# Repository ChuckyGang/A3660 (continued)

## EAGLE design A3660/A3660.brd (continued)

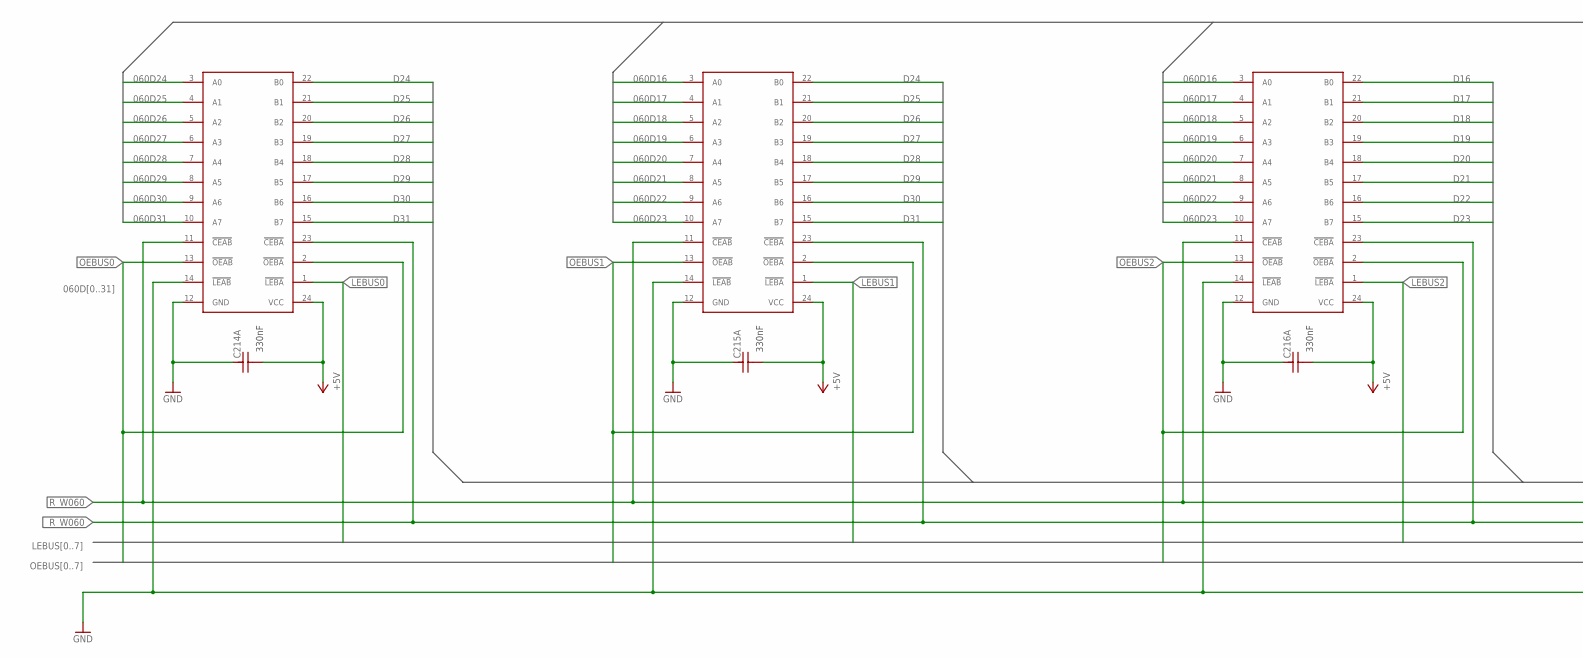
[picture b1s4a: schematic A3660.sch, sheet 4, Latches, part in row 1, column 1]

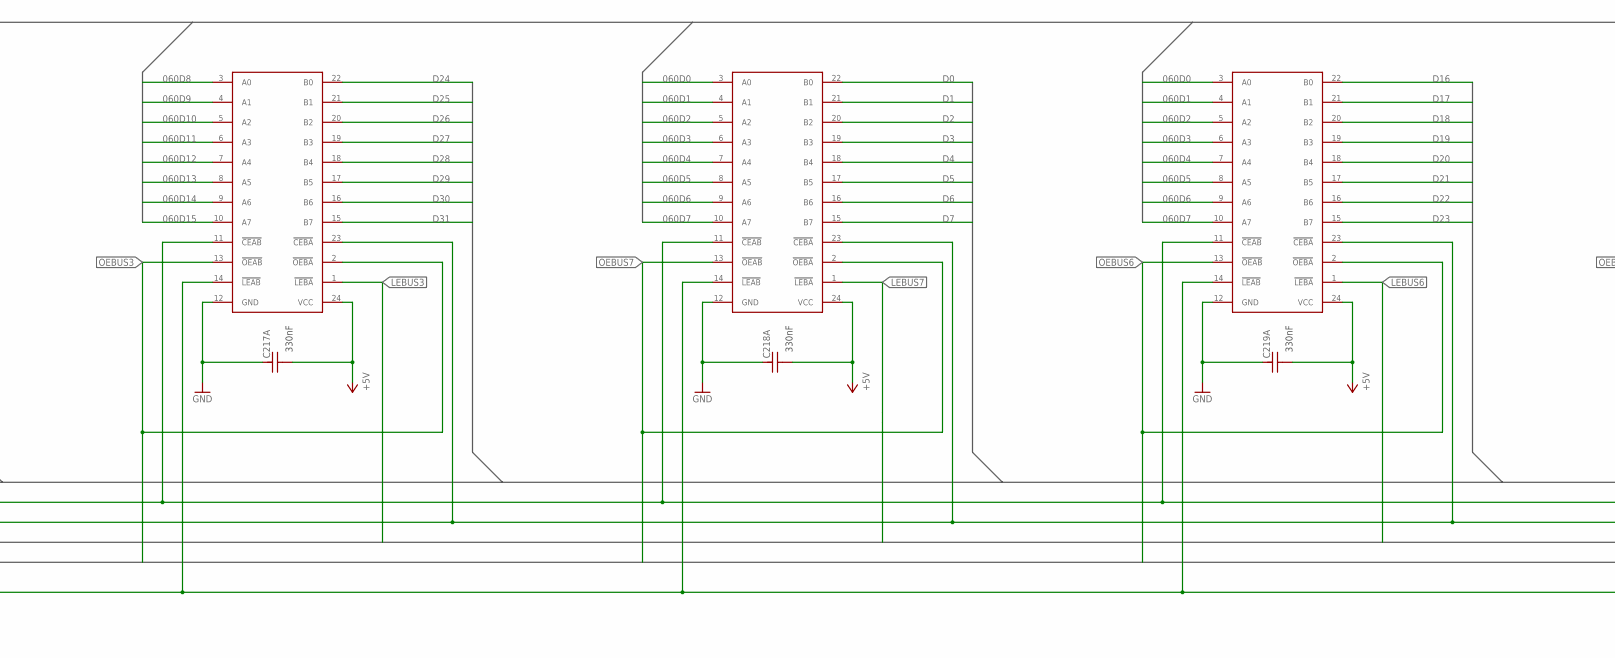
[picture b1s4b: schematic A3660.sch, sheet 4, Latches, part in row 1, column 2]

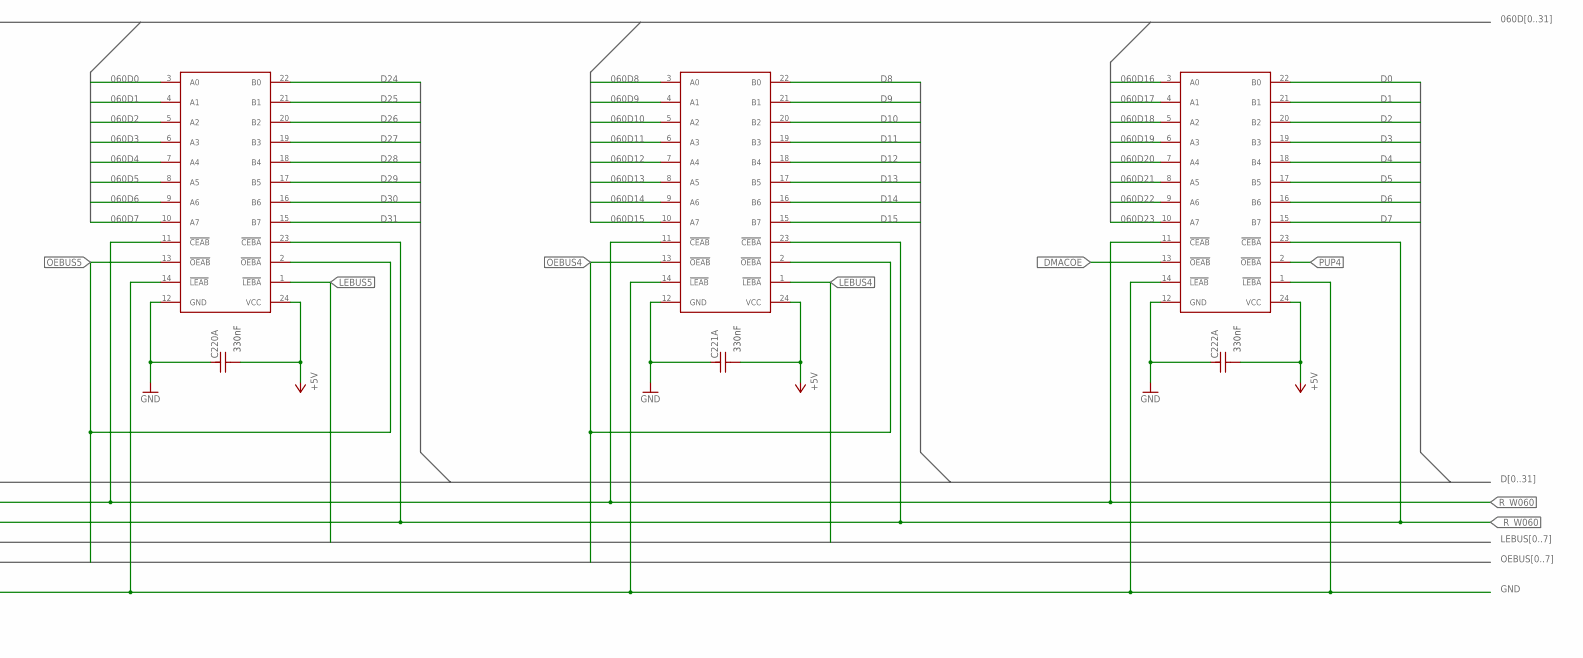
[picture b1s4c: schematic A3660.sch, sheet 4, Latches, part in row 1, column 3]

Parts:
C214A, C215A, C216A, C217A, C218A, C219A, C220A, C221A, C222A: 330nF; R0805
U214, U215, U216, U217, U218, U219, U220, U221, U222: 74FCT543A

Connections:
060D0: U218.3 (A0), U219.3 (A0), U220.3 (A0); also elsewhere on the board
060D1: U218.4 (A1), U219.4 (A1), U220.4 (A1); also elsewhere on the board
060D2: U218.5 (A2), U219.5 (A2), U220.5 (A2); also elsewhere on the board
060D3: U218.6 (A3), U219.6 (A3), U220.6 (A3); also elsewhere on the board
060D4: U218.7 (A4), U219.7 (A4), U220.7 (A4); also elsewhere on the board
060D5: U218.8 (A5), U219.8 (A5), U220.8 (A5); also elsewhere on the board
060D6: U218.9 (A6), U219.9 (A6), U220.9 (A6); also elsewhere on the board
060D7: U218.10 (A7), U219.10 (A7), U220.10 (A7); also elsewhere on the board
060D8: U217.3 (A0), U221.3 (A0); also elsewhere on the board
060D9: U217.4 (A1), U221.4 (A1); also elsewhere on the board
060D10: U217.5 (A2), U221.5 (A2); also elsewhere on the board
060D11: U217.6 (A3), U221.6 (A3); also elsewhere on the board
060D12: U217.7 (A4), U221.7 (A4); also elsewhere on the board
060D13: U217.8 (A5), U221.8 (A5); also elsewhere on the board
060D14: U217.9 (A6), U221.9 (A6); also elsewhere on the board
060D15: U217.10 (A7), U221.10 (A7); also elsewhere on the board
060D16: U215.3 (A0), U216.3 (A0), U222.3 (A0); also elsewhere on the board
060D17: U215.4 (A1), U216.4 (A1), U222.4 (A1); also elsewhere on the board
060D18: U215.5 (A2), U216.5 (A2), U222.5 (A2); also elsewhere on the board
060D19: U215.6 (A3), U216.6 (A3), U222.6 (A3); also elsewhere on the board
060D20: U215.7 (A4), U216.7 (A4), U222.7 (A4); also elsewhere on the board
060D21: U215.8 (A5), U216.8 (A5), U222.8 (A5); also elsewhere on the board
060D22: U215.9 (A6), U216.9 (A6), U222.9 (A6); also elsewhere on the board
060D23: U215.10 (A7), U216.10 (A7), U222.10 (A7); also elsewhere on the board
060D24: U214.3 (A0); also elsewhere on the board
060D25: U214.4 (A1); also elsewhere on the board
060D26: U214.5 (A2); also elsewhere on the board
060D27: U214.6 (A3); also elsewhere on the board
060D28: U214.7 (A4); also elsewhere on the board
060D29: U214.8 (A5); also elsewhere on the board
060D30: U214.9 (A6); also elsewhere on the board
060D31: U214.10 (A7); also elsewhere on the board
+5V: C214A.2, C215A.2, C216A.2, C217A.2, C218A.2, C219A.2, C220A.2, C221A.2, C222A.2, U214.24 (VCC), U215.24 (VCC), U216.24 (VCC), U217.24 (VCC), U218.24 (VCC), U219.24 (VCC), U220.24 (VCC), U221.24 (VCC), U222.24 (VCC); also elsewhere on the board
D0: U218.22 (B0), U222.22 (B0); also elsewhere on the board
D1: U218.21 (B1), U222.21 (B1); also elsewhere on the board
D2: U218.20 (B2), U222.20 (B2); also elsewhere on the board
D3: U218.19 (B3), U222.19 (B3); also elsewhere on the board
D4: U218.18 (B4), U222.18 (B4); also elsewhere on the board
D5: U218.17 (B5), U222.17 (B5); also elsewhere on the board
D6: U218.16 (B6), U222.16 (B6); also elsewhere on the board
D7: U218.15 (B7), U222.15 (B7); also elsewhere on the board
D8: U221.22 (B0); also elsewhere on the board
D9: U221.21 (B1); also elsewhere on the board
D10: U221.20 (B2); also elsewhere on the board
D11: U221.19 (B3); also elsewhere on the board
D12: U221.18 (B4); also elsewhere on the board
D13: U221.17 (B5); also elsewhere on the board
D14: U221.16 (B6); also elsewhere on the board
D15: U221.15 (B7); also elsewhere on the board
D16: U216.22 (B0), U219.22 (B0); also elsewhere on the board
D17: U216.21 (B1), U219.21 (B1); also elsewhere on the board
D18: U216.20 (B2), U219.20 (B2); also elsewhere on the board
D19: U216.19 (B3), U219.19 (B3); also elsewhere on the board
D20: U216.18 (B4), U219.18 (B4); also elsewhere on the board
D21: U216.17 (B5), U219.17 (B5); also elsewhere on the board
D22: U216.16 (B6), U219.16 (B6); also elsewhere on the board
D23: U216.15 (B7), U219.15 (B7); also elsewhere on the board
D24: U214.22 (B0), U215.22 (B0), U217.22 (B0), U220.22 (B0); also elsewhere on the board
D25: U214.21 (B1), U215.21 (B1), U217.21 (B1), U220.21 (B1); also elsewhere on the board
D26: U214.20 (B2), U215.20 (B2), U217.20 (B2), U220.20 (B2); also elsewhere on the board
D27: U214.19 (B3), U215.19 (B3), U217.19 (B3), U220.19 (B3); also elsewhere on the board
D28: U214.18 (B4), U215.18 (B4), U217.18 (B4), U220.18 (B4); also elsewhere on the board
D29: U214.17 (B5), U215.17 (B5), U217.17 (B5), U220.17 (B5); also elsewhere on the board
D30: U214.16 (B6), U215.16 (B6), U217.16 (B6), U220.16 (B6); also elsewhere on the board
D31: U214.15 (B7), U215.15 (B7), U217.15 (B7), U220.15 (B7); also elsewhere on the board
GND: C214A.1, C215A.1, C216A.1, C217A.1, C218A.1, C219A.1, C220A.1, C221A.1, C222A.1, U214.12 (GND), U214.14 (!LEAB), U215.12 (GND), U215.14 (!LEAB), U216.12 (GND), U216.14 (!LEAB), U217.12 (GND), U217.14 (!LEAB), U218.12 (GND), U218.14 (!LEAB), U219.12 (GND), U219.14 (!LEAB), U220.12 (GND), U220.14 (!LEAB), U221.12 (GND), U221.14 (!LEAB), U222.1 (!LEBA), U222.12 (GND), U222.14 (!LEAB); also elsewhere on the board
LEBUS0: U214.1 (!LEBA); also elsewhere on the board
LEBUS1: U215.1 (!LEBA); also elsewhere on the board
LEBUS2: U216.1 (!LEBA); also elsewhere on the board
LEBUS3: U217.1 (!LEBA); also elsewhere on the board
LEBUS4: U221.1 (!LEBA); also elsewhere on the board
LEBUS5: U220.1 (!LEBA); also elsewhere on the board
LEBUS6: U219.1 (!LEBA); also elsewhere on the board
LEBUS7: U218.1 (!LEBA); also elsewhere on the board
OEBUS0: U214.2 (!OEBA), U214.13 (!OEAB); also elsewhere on the board
OEBUS1: U215.2 (!OEBA), U215.13 (!OEAB); also elsewhere on the board
OEBUS2: U216.2 (!OEBA), U216.13 (!OEAB); also elsewhere on the board
OEBUS3: U217.2 (!OEBA), U217.13 (!OEAB); also elsewhere on the board
OEBUS4: U221.2 (!OEBA), U221.13 (!OEAB); also elsewhere on the board
OEBUS5: U220.2 (!OEBA), U220.13 (!OEAB); also elsewhere on the board
OEBUS6: U219.2 (!OEBA), U219.13 (!OEAB); also elsewhere on the board
OEBUS7: U218.2 (!OEBA), U218.13 (!OEAB); also elsewhere on the board
PUP4: U222.2 (!OEBA); also elsewhere on the board
R_W060: U214.11 (!CEAB), U215.11 (!CEAB), U216.11 (!CEAB), U217.11 (!CEAB), U218.11 (!CEAB), U219.11 (!CEAB), U220.11 (!CEAB), U221.11 (!CEAB), U222.11 (!CEAB); also elsewhere on the board
_DMACOE: U222.13 (!OEAB); also elsewhere on the board
_R_W060: U214.23 (!CEBA), U215.23 (!CEBA), U216.23 (!CEBA), U217.23 (!CEBA), U218.23 (!CEBA), U219.23 (!CEBA), U220.23 (!CEBA), U221.23 (!CEBA), U222.23 (!CEBA); also elsewhere on the board

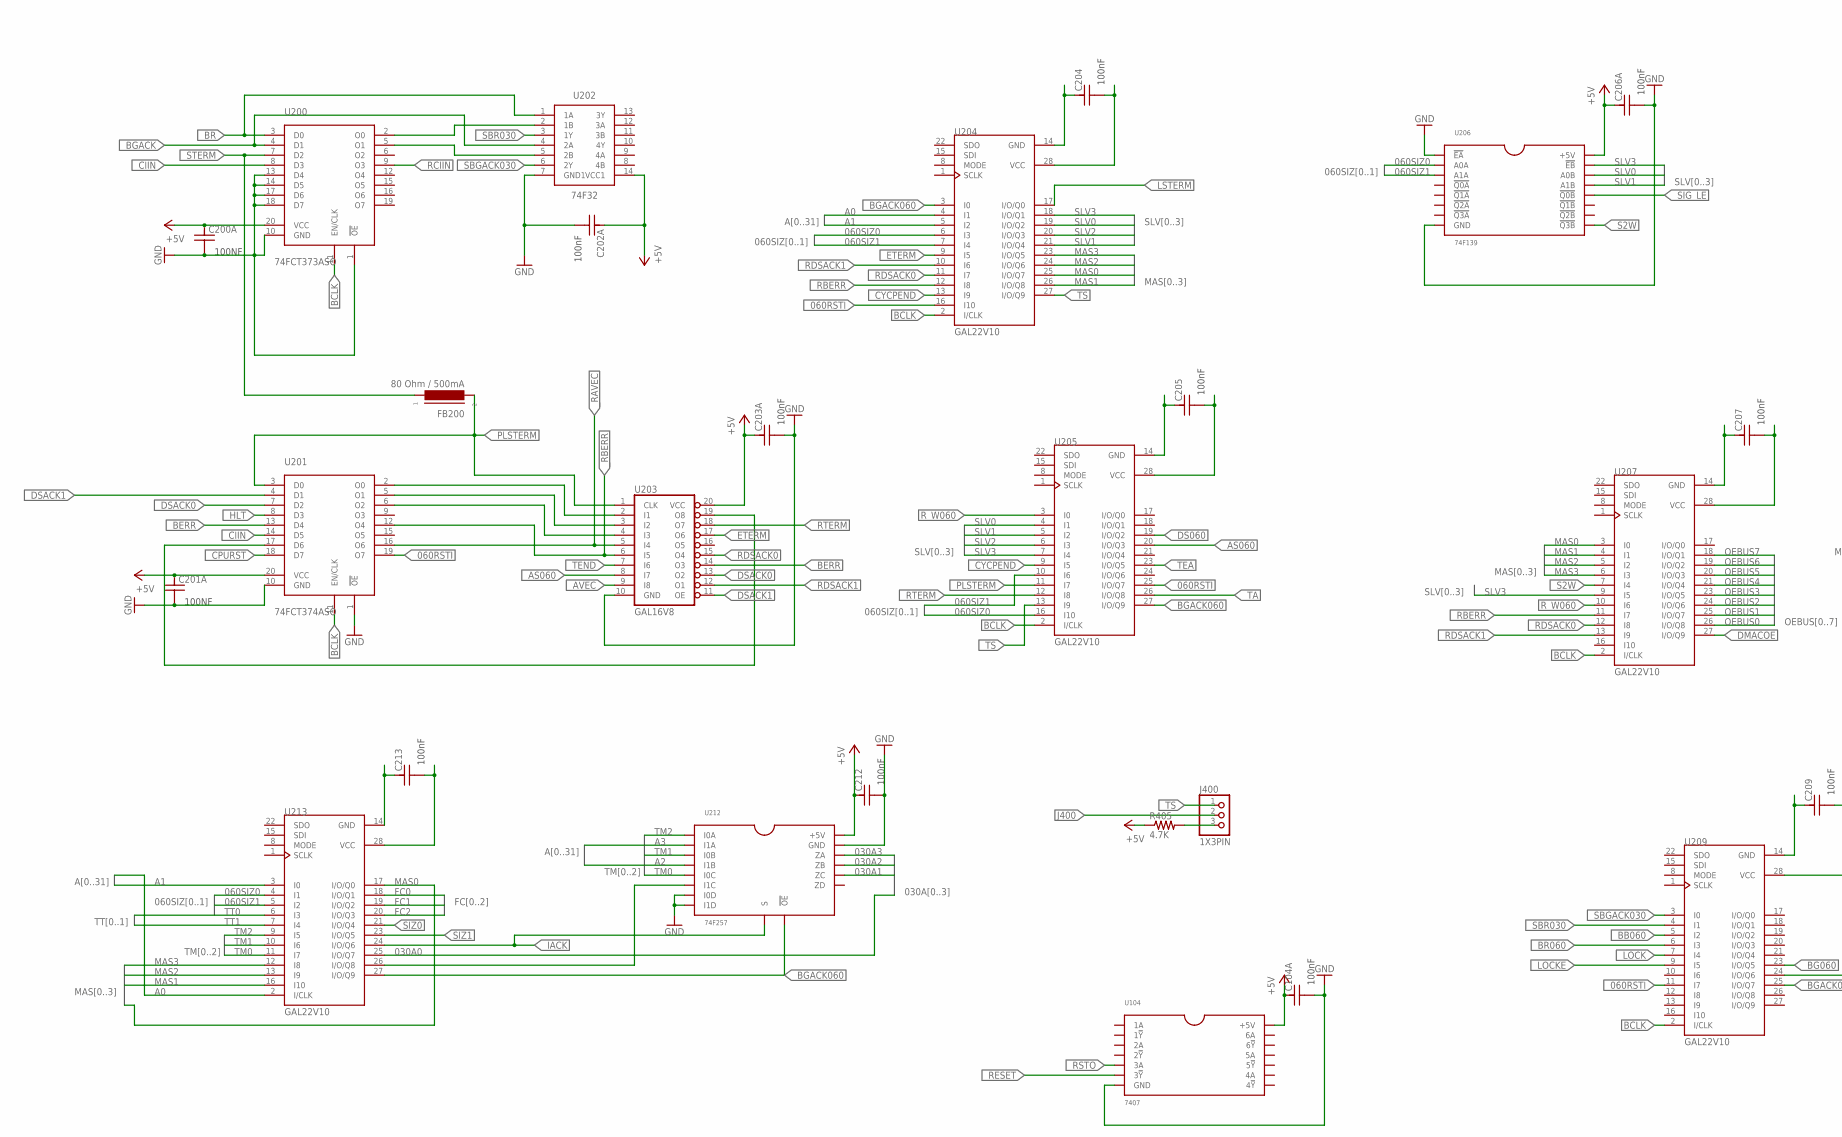
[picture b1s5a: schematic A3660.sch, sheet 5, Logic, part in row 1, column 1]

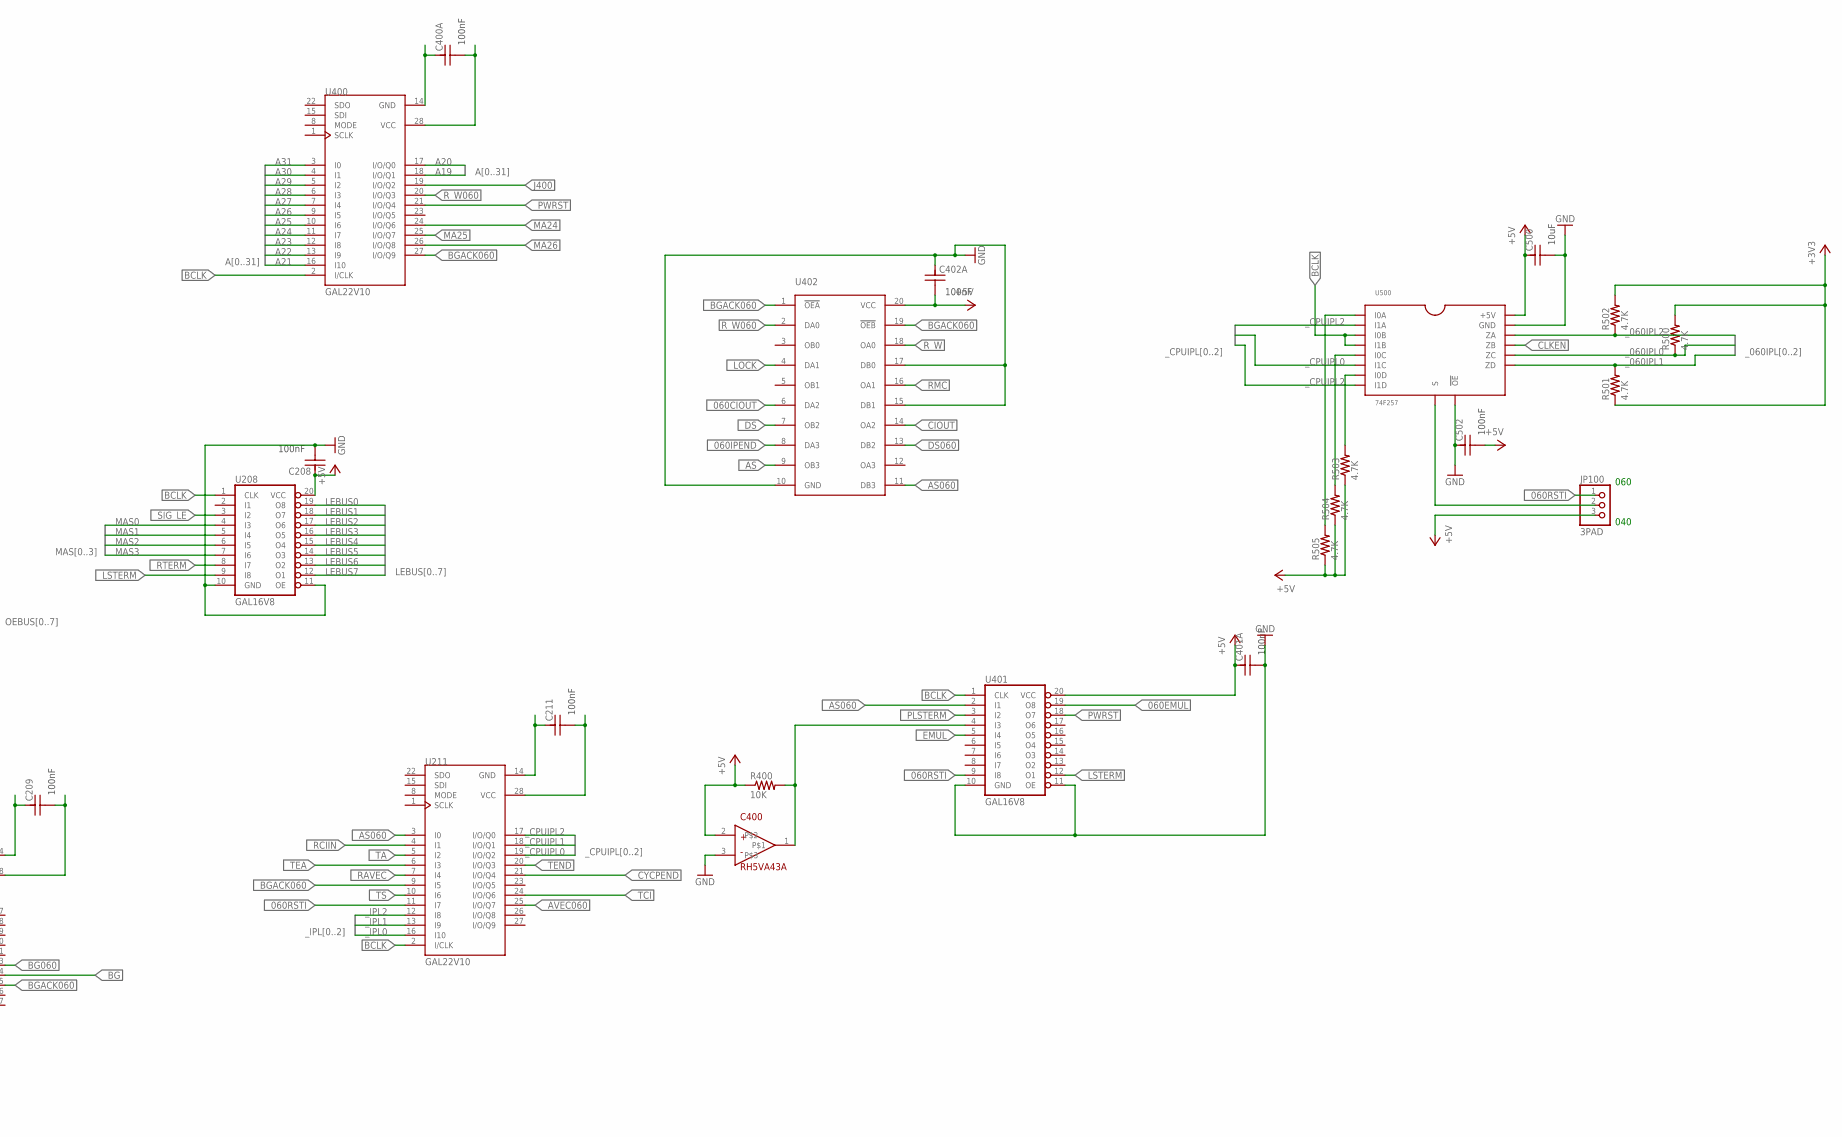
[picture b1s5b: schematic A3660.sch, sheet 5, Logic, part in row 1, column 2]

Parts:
C104A, C202A, C203A, C204, C205, C206A, C207, C208, C209, C211, C212, C213, C400A, C401A, C402A, C502: 100nF; R0805
C200A, C201A: 100NF; R0805
C400: RH5VA43A
C500: 10uF; R0805
FB200: 80 Ohm / 500mA; FERRITE
J400: 1X3PIN
JP100: 3PAD
R400: 10K; R0805
R405, R500, R501, R502, R503, R504, R505: 4.7K; R0805
U104: 7407
U200: 74FCT373ASO
U201: 74FCT374ASO
U202: 74F32
U203, U208, U401: GAL16V8
U204, U205, U207, U209, U211, U213, U400: GAL22V10
U206: 74F139
U212, U500: 74F257
U402: 74FCT244A

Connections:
030A0: U213.25 (I/O/Q7); also elsewhere on the board
030A1: U212.12 (ZC); also elsewhere on the board
030A2: U212.7 (ZB); also elsewhere on the board
030A3: U212.4 (ZA); also elsewhere on the board
060SIZ0: U204.6 (I3), U205.16 (I10), U206.2 (A0A), U213.4 (I1); also elsewhere on the board
060SIZ1: U204.7 (I4), U205.10 (I6), U206.3 (A1A), U213.5 (I2); also elsewhere on the board
+3V3: R500.2, R501.1, R502.2; also elsewhere on the board
+5V: C104A.1, C200A.1, C201A.1, C202A.1, C203A.1, C206A.1, C208.1, C212.1, C400.2, C401A.1, C402A.2, C500.1, C502.2, JP100.3, R400.1, R405.1, R503.1, R504.1, R505.1, U104.VCC (+5V), U200.20 (VCC), U201.20 (VCC), U202.14 (VCC1), U203.20 (VCC), U206.16 (+5V), U208.20 (VCC), U212.16 (+5V), U401.20 (VCC), U402.20 (VCC), U500.16 (+5V); also elsewhere on the board
A0: U204.4 (I1), U213.2 (I/CLK); also elsewhere on the board
A1: U204.5 (I2), U213.3 (I0); also elsewhere on the board
A2: U212.6 (I1B); also elsewhere on the board
A3: U212.3 (I1A); also elsewhere on the board
A19: U400.18 (I/O/Q1); also elsewhere on the board
A20: U400.17 (I/O/Q0); also elsewhere on the board
A21: U400.16 (I10); also elsewhere on the board
A22: U400.13 (I9); also elsewhere on the board
A23: U400.12 (I8); also elsewhere on the board
A24: U400.11 (I7); also elsewhere on the board
A25: U400.10 (I6); also elsewhere on the board
A26: U400.9 (I5); also elsewhere on the board
A27: U400.7 (I4); also elsewhere on the board
A28: U400.6 (I3); also elsewhere on the board
A29: U400.5 (I2); also elsewhere on the board
A30: U400.4 (I1); also elsewhere on the board
A31: U400.3 (I0); also elsewhere on the board
BCLK: U200.11 (EN/CLK), U201.11 (EN/CLK), U204.2 (I/CLK), U205.2 (I/CLK), U207.2 (I/CLK), U208.1 (CLK), U209.2 (I/CLK), U211.2 (I/CLK), U400.2 (I/CLK), U401.1 (CLK), U500.5 (I0B), U500.6 (I1B); also elsewhere on the board
CPUSEL: JP100.2, U500.1 (S)
FC0: U213.18 (I/O/Q1); also elsewhere on the board
FC1: U213.19 (I/O/Q2); also elsewhere on the board
FC2: U213.20 (I/O/Q3); also elsewhere on the board
GND: C104A.2, C200A.2, C201A.2, C202A.2, C203A.2, C206A.2, C208.2, C212.2, C400.3, C401A.2, C402A.1, C500.2, C502.1, U104.GND, U200.1 (!OE), U200.10 (GND), U200.13 (D4), U200.14 (D5), U200.17 (D6), U200.18 (D7), U201.1 (!OE), U201.10 (GND), U202.7 (GND1), U203.10 (GND), U206.1 (!EA), U206.8 (GND), U208.10 (GND), U208.11 (OE), U212.8 (GND), U212.10 (I1D), U212.11 (I0D), U401.10 (GND), U401.11 (OE), U402.10 (GND), U402.15 (DB1), U402.17 (DB0), U500.8 (GND), U500.15 (!OE); also elsewhere on the board
J400: J400.2, U400.19 (I/O/Q2)
LEBUS0: U208.19 (O8); also elsewhere on the board
LEBUS1: U208.18 (O7); also elsewhere on the board
LEBUS2: U208.17 (O6); also elsewhere on the board
LEBUS3: U208.16 (O5); also elsewhere on the board
LEBUS4: U208.15 (O4); also elsewhere on the board
LEBUS5: U208.14 (O3); also elsewhere on the board
LEBUS6: U208.13 (O2); also elsewhere on the board
LEBUS7: U208.12 (O1); also elsewhere on the board
MA24: U400.24 (I/O/Q6); also elsewhere on the board
MA25: U400.25 (I/O/Q7); also elsewhere on the board
MA26: U400.26 (I/O/Q8); also elsewhere on the board
MAS0: U204.25 (I/O/Q7), U207.3 (I0), U208.4 (I3), U213.17 (I/O/Q0)
MAS1: U204.26 (I/O/Q8), U207.4 (I1), U208.5 (I4), U213.16 (I10)
MAS2: U204.24 (I/O/Q6), U207.5 (I2), U208.6 (I5), U213.13 (I9)
MAS3: U204.23 (I/O/Q5), U207.6 (I3), U208.7 (I6), U213.12 (I8)
unnamed: C400.1, R400.2, U401.4 (I3)
unnamed: U201.17 (D6), U203.19 (O8)
unnamed: J400.3, R405.2
unnamed: R503.2, U500.11 (I0D)
unnamed: R504.2, U500.14 (I0C)
unnamed: U200.2 (O0), U202.2 (1B)
unnamed: U200.5 (O1), U202.5 (2B)
unnamed: U201.2 (O0), U203.2 (I1)
unnamed: U201.5 (O1), U203.3 (I2)
unnamed: U201.6 (O2), U203.4 (I3)
unnamed: C204.1, U204.14 (GND)
unnamed: C204.2, U204.28 (VCC)
unnamed: C207.1, U207.14 (GND)
unnamed: C207.2, U207.28 (VCC)
unnamed: C213.1, U213.14 (GND)
unnamed: C213.2, U213.28 (VCC)
unnamed: U212.13 (I1C), U213.26 (I/O/Q8)
unnamed: C209.1, U209.14 (GND)
unnamed: C209.2, U209.28 (VCC)
unnamed: C211.1, U211.14 (GND)
unnamed: C211.2, U211.28 (VCC)
unnamed: C400A.1, U400.14 (GND)
unnamed: C400A.2, U400.28 (VCC)
unnamed: R505.2, U500.2 (I0A)
unnamed: C205.1, U205.14 (GND)
unnamed: C205.2, U205.28 (VCC)
OEBUS0: U207.26 (I/O/Q8); also elsewhere on the board
OEBUS1: U207.25 (I/O/Q7); also elsewhere on the board
OEBUS2: U207.24 (I/O/Q6); also elsewhere on the board
OEBUS3: U207.23 (I/O/Q5); also elsewhere on the board
OEBUS4: U207.21 (I/O/Q4); also elsewhere on the board
OEBUS5: U207.20 (I/O/Q3); also elsewhere on the board
OEBUS6: U207.19 (I/O/Q2); also elsewhere on the board
OEBUS7: U207.18 (I/O/Q1); also elsewhere on the board
R_W: U402.18 (OA0); also elsewhere on the board
R_W060: U205.3 (I0), U207.10 (I6), U400.20 (I/O/Q3), U402.2 (DA0); also elsewhere on the board
SIZ0: U213.21 (I/O/Q4); also elsewhere on the board
SIZ1: U213.23 (I/O/Q5); also elsewhere on the board
SLV0: U204.19 (I/O/Q2), U205.4 (I1), U206.14 (A0B)
SLV1: U204.21 (I/O/Q4), U205.5 (I2), U206.13 (A1B)
SLV2: U204.20 (I/O/Q3), U205.6 (I3)
SLV3: U204.18 (I/O/Q1), U205.7 (I4), U206.15 (!EB), U207.9 (I5)
TM0: U212.14 (I0C), U213.11 (I7); also elsewhere on the board
TM1: U212.5 (I0B), U213.10 (I6); also elsewhere on the board
TM2: U212.2 (I0A), U213.9 (I5); also elsewhere on the board
TT0: U213.6 (I3); also elsewhere on the board
TT1: U213.7 (I4); also elsewhere on the board
_060CIOUT: U402.6 (DA2); also elsewhere on the board
_060EMUL: U401.19 (O8); also elsewhere on the board
_060IPEND: U402.8 (DA3); also elsewhere on the board
_060IPL0: R500.1, U500.12 (ZC); also elsewhere on the board
_060IPL1: R501.2, U500.9 (ZD); also elsewhere on the board
_060IPL2: R502.1, U500.4 (ZA); also elsewhere on the board
_060RSTI: JP100.1, U201.19 (O7), U204.16 (I10), U205.25 (I/O/Q7), U209.11 (I7), U211.11 (I7), U401.9 (I8); also elsewhere on the board
_AS: U402.9 (OB3); also elsewhere on the board
_AS060: U203.8 (I7), U205.20 (I/O/Q3), U211.3 (I0), U401.2 (I1), U402.11 (DB3)
_AVEC: U203.9 (I8); also elsewhere on the board
_AVEC060: U211.25 (I/O/Q7); also elsewhere on the board
_BB060: U209.5 (I2); also elsewhere on the board
_BERR: U201.13 (D4), U203.14 (O3); also elsewhere on the board
_BG: U209.24 (I/O/Q6); also elsewhere on the board
_BG060: U209.23 (I/O/Q5); also elsewhere on the board
_BGACK: U200.4 (D1), U202.4 (2A); also elsewhere on the board
_BGACK060: U204.3 (I0), U205.27 (I/O/Q9), U209.25 (I/O/Q7), U211.9 (I5), U212.15 (!OE), U213.27 (I/O/Q9), U400.27 (I/O/Q9), U402.1 (!OEA), U402.19 (!OEB)
_BR: U200.3 (D0), U202.1 (1A); also elsewhere on the board
_BR060: U209.6 (I3); also elsewhere on the board
_CIIN: U200.8 (D3), U201.14 (D5); also elsewhere on the board
_CIOUT: U402.14 (OA2); also elsewhere on the board
_CLKEN: U500.7 (ZB); also elsewhere on the board
_CPUIPL0: U211.19 (I/O/Q2), U500.13 (I1C)
_CPUIPL1: U211.18 (I/O/Q1)
_CPUIPL2: U211.17 (I/O/Q0), U500.3 (I1A), U500.10 (I1D)
_CPURST: U201.18 (D7); also elsewhere on the board
_CYCPEND: U204.13 (I9), U205.9 (I5), U211.21 (I/O/Q4)
_DMACOE: U207.27 (I/O/Q9); also elsewhere on the board
_DS: U402.7 (OB2); also elsewhere on the board
_DS060: U205.19 (I/O/Q2), U402.13 (DB2)
_DSACK0: U201.7 (D2), U203.13 (O2); also elsewhere on the board
_DSACK1: U201.4 (D1), U203.11 (OE); also elsewhere on the board
_EMUL: U401.5 (I4); also elsewhere on the board
_ETERM: U203.17 (O6), U204.9 (I5)
_HLT: U201.8 (D3); also elsewhere on the board
_IACK: U212.1 (S), U213.24 (I/O/Q6)
_IPL0: U211.16 (I10); also elsewhere on the board
_IPL1: U211.13 (I9); also elsewhere on the board
_IPL2: U211.12 (I8); also elsewhere on the board
_LOCK: U209.7 (I4), U402.4 (DA1); also elsewhere on the board
_LOCKE: U209.9 (I5); also elsewhere on the board
_LSTERM: U204.17 (I/O/Q0), U208.9 (I8), U401.12 (O1)
_PLSTERM: FB200.2, U201.3 (D0), U203.1 (CLK), U205.11 (I7), U401.3 (I2); also elsewhere on the board
_PWRST: U400.21 (I/O/Q4), U401.18 (O7)
_RAVEC: U201.16 (O6), U203.5 (I4), U211.7 (I4)
_RBERR: U201.12 (O4), U203.6 (I5), U204.12 (I8), U207.11 (I7)
_RCIIN: U200.9 (O3), U211.4 (I1)
_RDSACK0: U203.15 (O4), U204.11 (I7), U207.12 (I8)
_RDSACK1: U203.12 (O1), U204.10 (I6), U207.13 (I9)
_RESET: U104.5 (3!Y); also elsewhere on the board
_RMC: U402.16 (OA1); also elsewhere on the board
_RSTO: U104.6 (3A); also elsewhere on the board
_RTERM: U203.18 (O7), U205.12 (I8), U208.8 (I7)
_S2W: U206.9 (!Q3B), U207.7 (I4)
_SBGACK030: U202.6 (2Y), U209.3 (I0)
_SBR030: U202.3 (1Y), U209.4 (I1)
_SIG_LE: U206.12 (!Q0B), U208.3 (I2)
_STERM: FB200.1, U200.7 (D2)
_TA: U205.26 (I/O/Q8), U211.5 (I2); also elsewhere on the board
_TCI: U211.24 (I/O/Q6); also elsewhere on the board
_TEA: U205.23 (I/O/Q5), U211.6 (I3); also elsewhere on the board
_TEND: U203.7 (I6), U211.20 (I/O/Q3)
_TS: J400.1, U204.27 (I/O/Q9), U205.13 (I9), U211.10 (I6); also elsewhere on the board

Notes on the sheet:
040
060

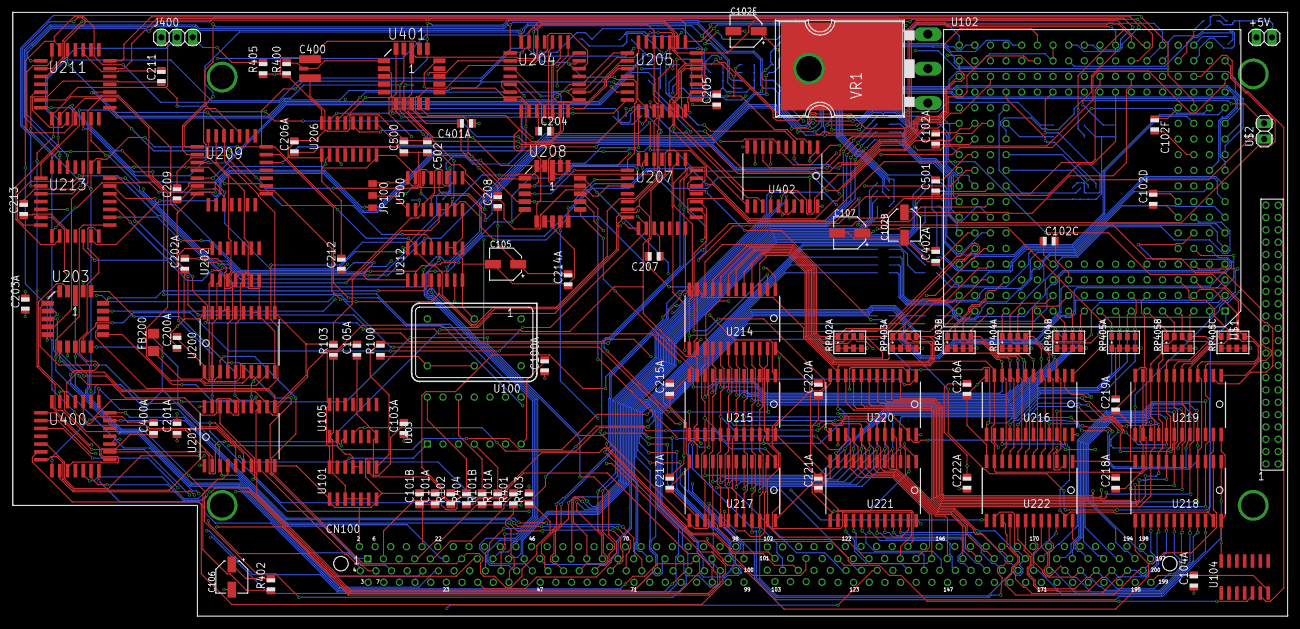
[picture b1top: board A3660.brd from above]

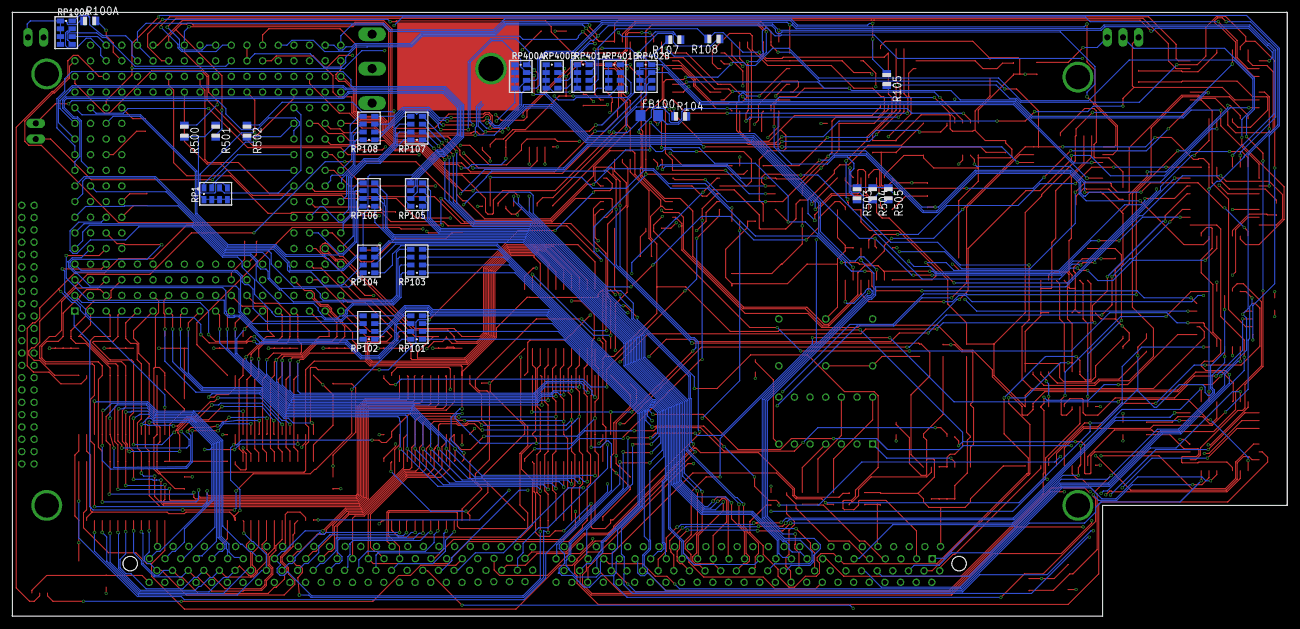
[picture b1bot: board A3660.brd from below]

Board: 4 copper layers, 207.0 x 98.0 mm, 130 parts (27 on the bottom side), 295 nets.

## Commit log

2017-11-19 First release, empty board and most devices in library. With help from Edu Arana
2017-11-20 Added and changed some in library. Added schematics for CPU, Cpuclockdriver and some of the latches
2017-11-21 More stuff done.. some logic left.
2017-11-22 Most stuff is there. A lot of tidyup needed..
2017-11-26 A3640 schematics complete
2017-11-27 A3660 Complete and aprox-location of components. datasignals at bottom of cpu, address at side so it is not scattered around the board.
2017-11-30 Datalines routed,, most addresslines aswell
2017-12-04 Addresssignals complete, IPL etc working on
2017-12-21 Autoroute done
